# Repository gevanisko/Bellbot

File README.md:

# BellBot

This repository contains the hardware design files, documentation, and supporting resources for the BellBot project. BellBot is an autonomous luggage transportation robot intended to use sensing, mapping, wireless control, onboard data storage, and motor control to move luggage through indoor environments.

The hardware in this repository is developed across multiple board revisions. Each version is used to test, validate, and improve different parts of the system, including power regulation, peripheral integration, motor control, communication, and future onboard intelligence.

## Project Overview

The long-term goal of BellBot is to create a robotic luggage transportation system capable of navigating indoor environments. The system is designed around Simultaneous Localization and Mapping (SLAM), LiDAR sensing, inertial measurement, Bluetooth control, onboard logging, and multi-directional motor control.

Early board revisions focus on creating a reliable minimum viable product (MVP). Later revisions are intended to improve size, integration, efficiency, and performance.

## Core Goals

The BellBot hardware is designed to support:

- Autonomous navigation through mapped environments
- LiDAR-based obstacle detection and mapping
- Remote control through Bluetooth or another wireless interface
- Onboard storage for sensor data, logs, and system debugging
- Motor control for movement in a 2D plane
- Multiple regulated voltage rails for sensors, logic, and motors
- Expandability for future sensors, memory, and processing hardware

## Hardware Features

Across the project revisions, the BellBot hardware may include:

| Feature | Purpose |
|---|---|
| STM32 Microcontroller | Main control platform for peripherals, motor control, and system logic |
| LiDAR | 2D scanning for mapping, localization, and obstacle detection |
| IMU | Acceleration, angular velocity, magnetic field, and orientation sensing |
| Bluetooth / Wireless Module | Remote control, debugging, or wireless communication |
| SPI Flash / SD Storage | Onboard storage for sensor data and logs |
| Servo / Motor PWM Outputs | Control signals for the robot drive system |
| 3.3 V Rail | Logic-level supply for MCU and low-voltage peripherals |
| 5 V Rail | Peripheral and module power |
| 8 V Rail | Servo or motor power |
| I2C / SPI / UART / Quad-SPI Breakouts | Expansion for additional sensors, memory, or communication modules |
| Battery Charging and Protection | Portable operation and safe lithium-ion battery use |

Later iterations (V2 and onward) are looking to employ AI accelerated MCU chips (STM32 N6) with a reduced size and mainly using SMT components as opposed to through hole components

## Board Revisions

This repository is intended to support multiple hardware revisions. Each revision may include different component choices, layouts, and design improvements.

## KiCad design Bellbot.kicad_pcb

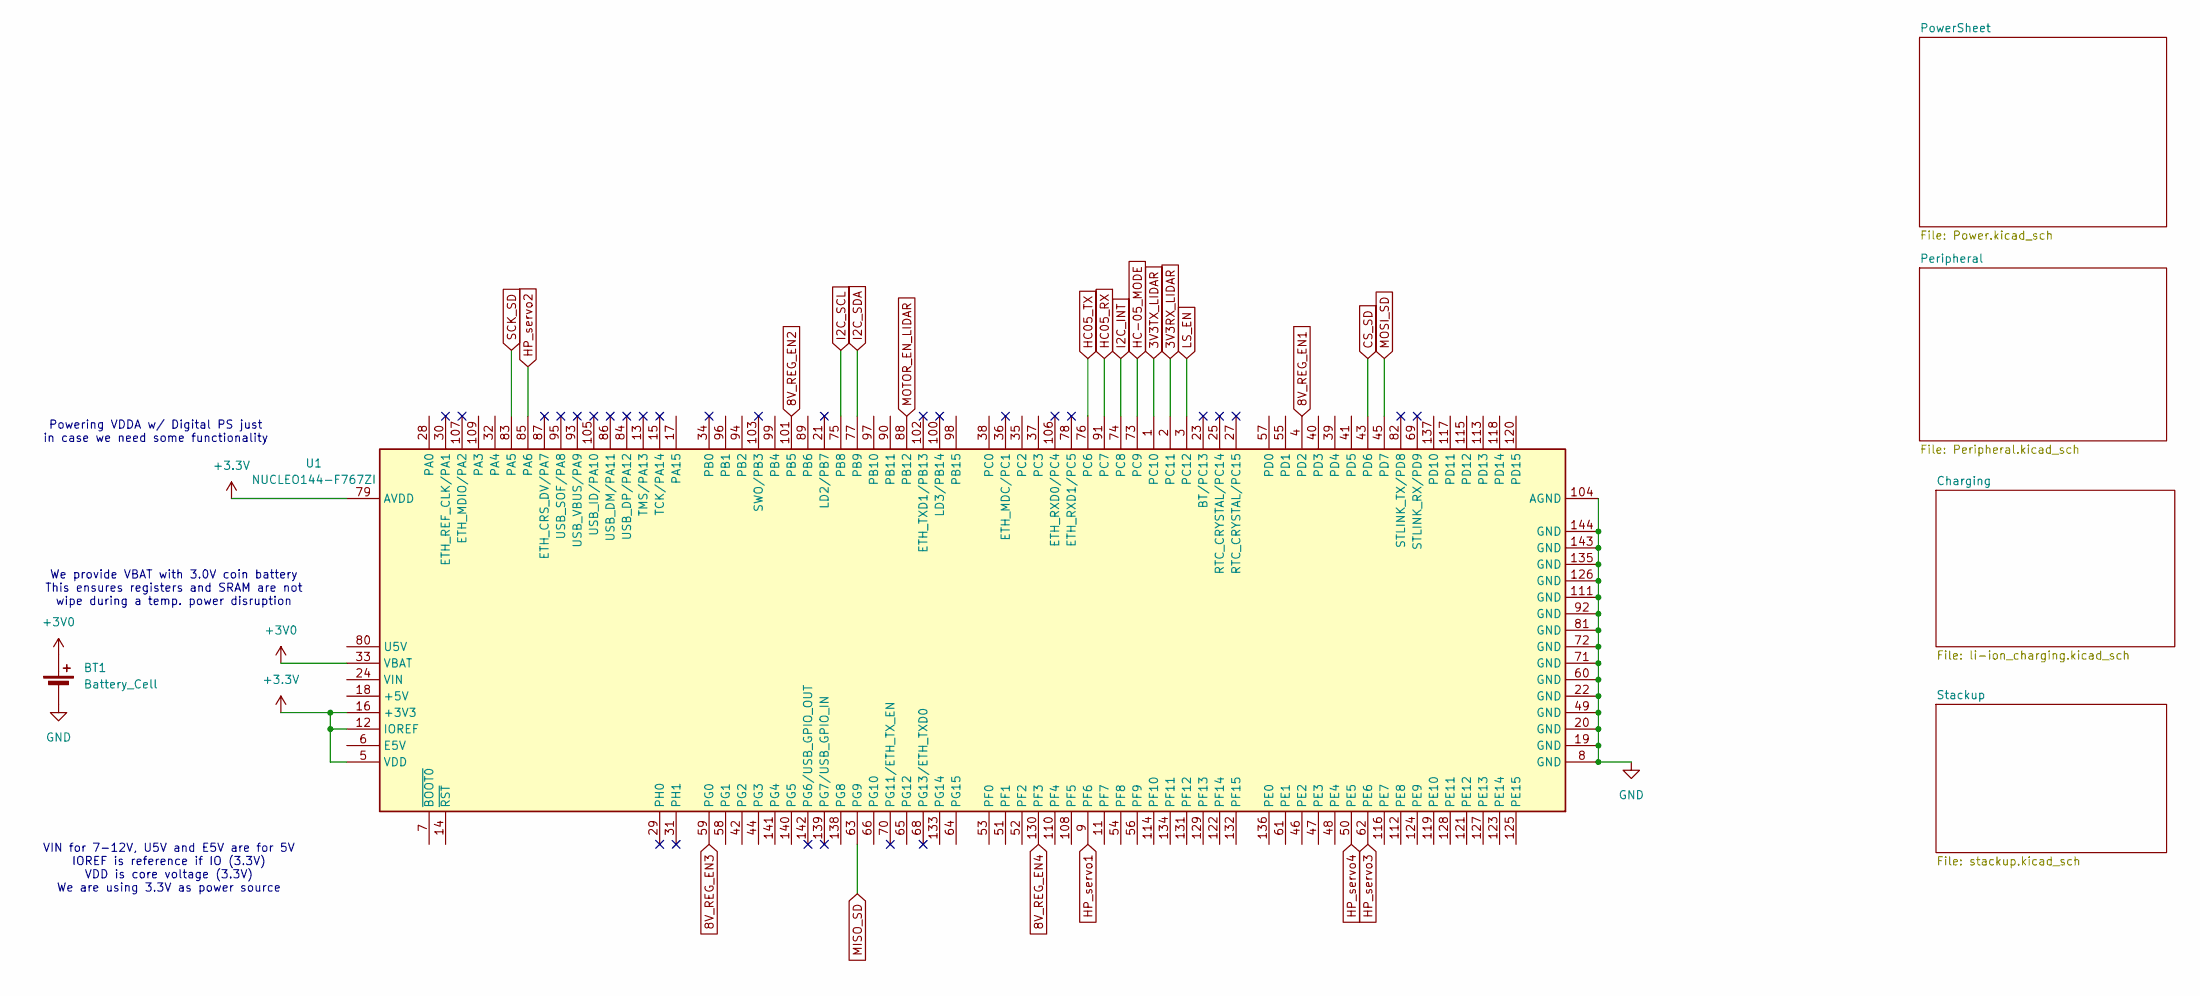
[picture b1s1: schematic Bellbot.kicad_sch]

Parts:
BT1: Battery_Cell; BatteryHolder_MPD_BC2003_1x2032
U1: NUCLEO144-F767ZI; ST_Morpho_Connector_144_STLink

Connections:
3V3RX_LIDAR: U1.2 (PC11); also elsewhere on the board
3V3TX_LIDAR: U1.1 (PC10); also elsewhere on the board
8V_REG_EN1: U1.4 (PD2); also elsewhere on the board
8V_REG_EN2: U1.101 (PB5); also elsewhere on the board
8V_REG_EN3: U1.59 (PG0); also elsewhere on the board
8V_REG_EN4: U1.130 (PF3); also elsewhere on the board
+3.3V: U1.5 (VDD), U1.12 (IOREF), U1.16 (+3V3), U1.79 (AVDD); also elsewhere on the board
+3V0: BT1.1 (+), U1.33 (VBAT)
/GPIO_Gen0: U1.116 (PE7)
/GPIO_Gen1: U1.112 (PE8)
/GPIO_Gen2: U1.124 (PE9)
/GPIO_Gen3: U1.119 (PE10)
/GPIO_Gen4: U1.128 (PE11)
/GPIO_Gen5: U1.121 (PE12)
/GPIO_Gen6: U1.127 (PE13)
/GPIO_Gen7: U1.123 (PE14)
/GPIO_Gen8: U1.125 (PE15)
CS_SD: U1.43 (PD6); also elsewhere on the board
GND: BT1.2 (-), U1.8 (GND), U1.19 (GND), U1.20 (GND), U1.22 (GND), U1.49 (GND), U1.60 (GND), U1.71 (GND), U1.72 (GND), U1.81 (GND), U1.92 (GND), U1.104 (AGND), U1.111 (GND), U1.126 (GND), U1.135 (GND), U1.143 (GND), U1.144 (GND); also elsewhere on the board
HC05_RX: U1.91 (PC7); also elsewhere on the board
HC05_TX: U1.76 (PC6); also elsewhere on the board
HC-05_MODE: U1.73 (PC9); also elsewhere on the board
HP_servo1: U1.9 (PF6); also elsewhere on the board
HP_servo2: U1.85 (PA6); also elsewhere on the board
HP_servo3: U1.62 (PE6); also elsewhere on the board
HP_servo4: U1.50 (PE5); also elsewhere on the board
I2C_Extra_SCL: U1.122 (PF14); also elsewhere on the board
I2C_Extra_SDA: U1.132 (PF15); also elsewhere on the board
I2C_INT: U1.74 (PC8); also elsewhere on the board
I2C_SCL: U1.75 (PB8); also elsewhere on the board
I2C_SDA: U1.77 (PB9); also elsewhere on the board
LS_EN: U1.3 (PC12)
MISO_SD: U1.63 (PG9); also elsewhere on the board
MOSI_SD: U1.45 (PD7); also elsewhere on the board
MOTOR_EN_LIDAR: U1.88 (PB12); also elsewhere on the board
unnamed 65: U1.44 (PG3); also elsewhere on the board
QUADSPI_CLK: U1.114 (PF10); also elsewhere on the board
QUADSPI_IO0: U1.54 (PF8); also elsewhere on the board
QUADSPI_IO1: U1.56 (PF9); also elsewhere on the board
QUADSPI_IO2: U1.46 (PE2); also elsewhere on the board
QUADSPI_IO3: U1.113 (PD13); also elsewhere on the board
QUADSPI_NCS: U1.97 (PB10); also elsewhere on the board
SCK_SD: U1.83 (PA5); also elsewhere on the board

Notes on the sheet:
VIN for 7-12V, U5V and E5V are for 5V IOREF is reference if IO (3.3V) VDD is core voltage (3.3V) We are using 3.3V as power source
Powering VDDA w/ Digital PS just in case we need some functionality
We provide VBAT with 3.0V coin battery This ensures registers and SRAM are not wipe during a temp. power disruption

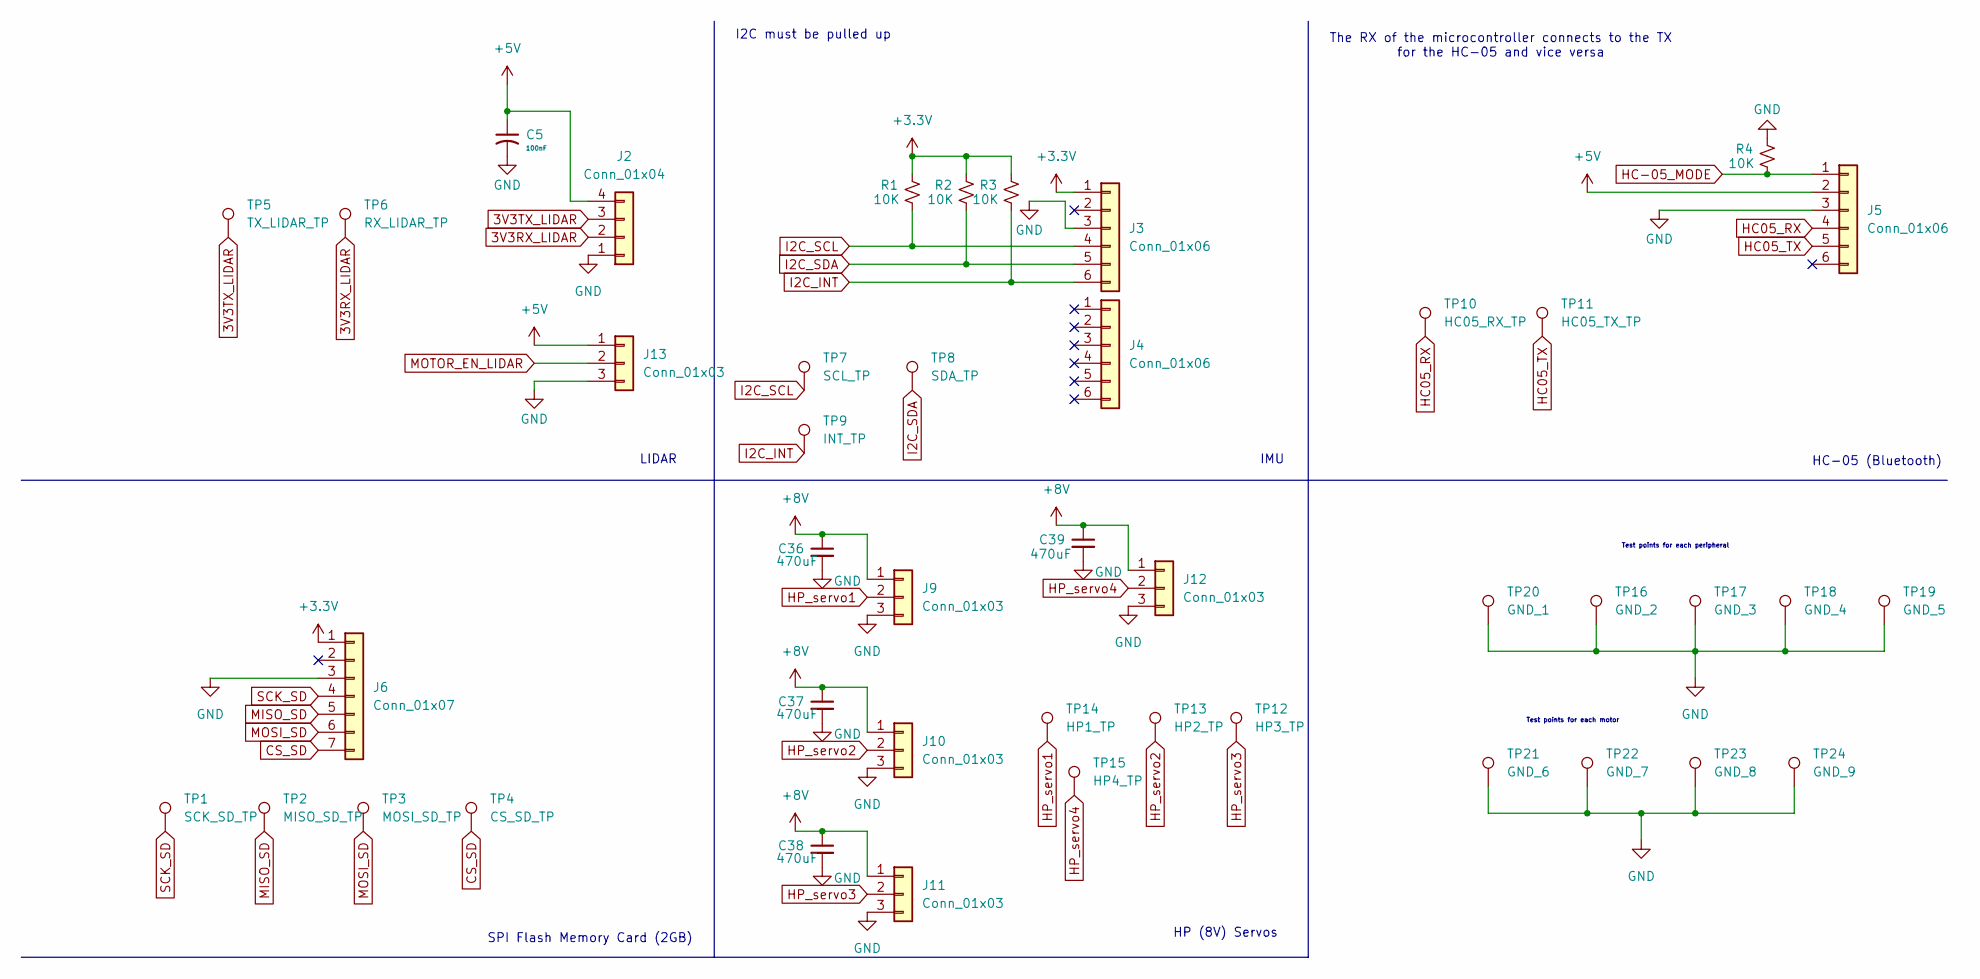
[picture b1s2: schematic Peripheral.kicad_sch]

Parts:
C5: 100nF; C_0603_1608Metric_Pad1.08x0.95mm_HandSolder
C36, C37, C38, C39: 470uF; C_0603_1608Metric_Pad1.08x0.95mm_HandSolder
J2: Conn_01x04; PinHeader_1x04_P2.54mm_Vertical
J3, J4, J5: Conn_01x06; PinHeader_1x06_P2.54mm_Vertical
J6: Conn_01x07; PinHeader_1x07_P2.54mm_Vertical
J9, J10, J11, J12, J13: Conn_01x03; PinHeader_1x03_P2.54mm_Vertical
R1, R2, R3, R4: 10K; R_0805_2012Metric_Pad1.20x1.40mm_HandSolder
TP1: SCK_SD_TP
TP2: MISO_SD_TP
TP3: MOSI_SD_TP
TP4: CS_SD_TP
TP5: TX_LIDAR_TP
TP6: RX_LIDAR_TP
TP7: SCL_TP
TP8: SDA_TP
TP9: INT_TP
TP10: HC05_RX_TP
TP11: HC05_TX_TP
TP12: HP3_TP
TP13: HP2_TP
TP14: HP1_TP
TP15: HP4_TP
TP16: GND_2
TP17: GND_3
TP18: GND_4
TP19: GND_5
TP20: GND_1
TP21: GND_6
TP22: GND_7
TP23: GND_8
TP24: GND_9

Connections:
3V3RX_LIDAR: J2.2, TP6.1 (1_1); also elsewhere on the board
3V3TX_LIDAR: J2.3, TP5.1 (1_1); also elsewhere on the board
+3.3V: J3.1, J6.1, R1.1, R2.1, R3.1; also elsewhere on the board
+5V: C5.1, J2.4, J5.2, J13.1; also elsewhere on the board
+8V: C36.1, C37.1, C38.1, C39.1, J9.1, J10.1, J11.1, J12.1; also elsewhere on the board
CS_SD: J6.7, TP4.1 (1_1); also elsewhere on the board
GND: C5.2, C36.2, C37.2, C38.2, C39.2, J2.1, J3.3, J5.3, J6.3, J9.3, J10.3, J11.3, J12.3, J13.3, R4.1, TP16.1 (1_1), TP17.1 (1_1), TP18.1 (1_1), TP19.1 (1_1), TP20.1 (1_1), TP21.1 (1_1), TP22.1 (1_1), TP23.1 (1_1), TP24.1 (1_1); also elsewhere on the board
HC05_RX: J5.4, TP10.1 (1_1); also elsewhere on the board
HC05_TX: J5.5, TP11.1 (1_1); also elsewhere on the board
HC-05_MODE: J5.1, R4.2; also elsewhere on the board
HP_servo1: J9.2, TP14.1 (1_1); also elsewhere on the board
HP_servo2: J10.2, TP13.1 (1_1); also elsewhere on the board
HP_servo3: J11.2, TP12.1 (1_1); also elsewhere on the board
HP_servo4: J12.2, TP15.1 (1_1); also elsewhere on the board
I2C_INT: J3.6, R3.2, TP9.1 (1_1); also elsewhere on the board
I2C_SCL: J3.4, R1.2, TP7.1 (1_1); also elsewhere on the board
I2C_SDA: J3.5, R2.2, TP8.1 (1_1); also elsewhere on the board
MISO_SD: J6.5, TP2.1 (1_1); also elsewhere on the board
MOSI_SD: J6.6, TP3.1 (1_1); also elsewhere on the board
MOTOR_EN_LIDAR: J13.2; also elsewhere on the board
SCK_SD: J6.4, TP1.1 (1_1); also elsewhere on the board

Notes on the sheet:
HC-05 (Bluetooth)
Test points for each motor
The RX of the microcontroller connects to the TX for the HC-05 and vice versa
Test points for each peripheral
IMU
LIDAR
HP (8V) Servos
I2C must be pulled up
SPI Flash Memory Card (2GB)

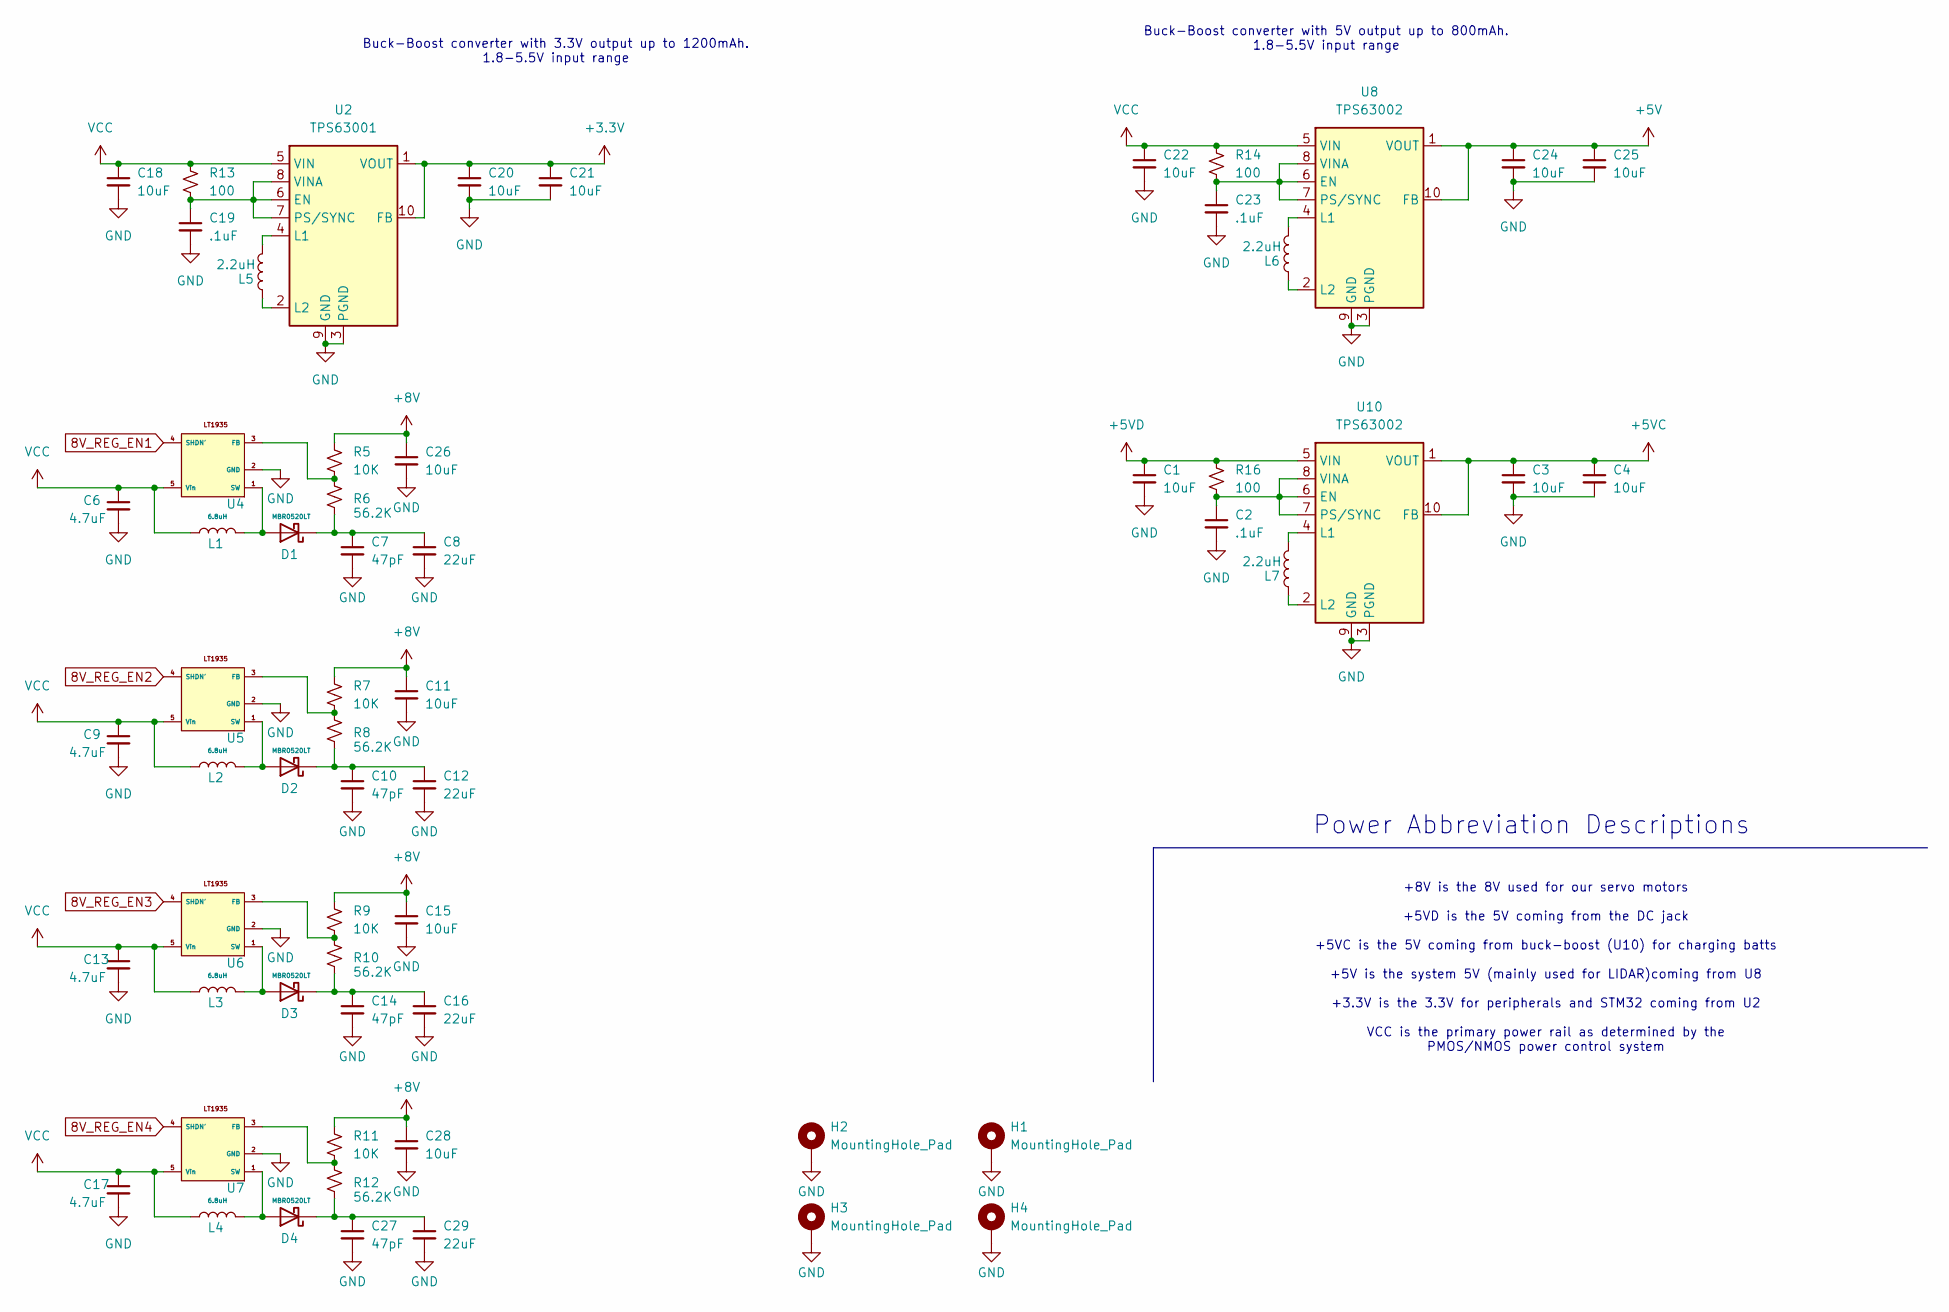
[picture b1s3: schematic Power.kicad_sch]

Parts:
C1, C3, C4, C11, C15, C18, C20, C21, C22, C24, C25, C26, C28: 10uF; C_0603_1608Metric_Pad1.08x0.95mm_HandSolder
C2, C19, C23: .1uF; C_0603_1608Metric_Pad1.08x0.95mm_HandSolder
C6, C9, C13, C17: 4.7uF; C_0603_1608Metric_Pad1.08x0.95mm_HandSolder
C7, C10, C14, C27: 47pF; C_0603_1608Metric_Pad1.08x0.95mm_HandSolder
C8, C12, C16, C29: 22uF; C_0603_1608Metric_Pad1.08x0.95mm_HandSolder
D1, D2, D3, D4: MBR0520LT; D_SOD-123
H1, H2, H3, H4: MountingHole_Pad; MountingHole_2.2mm_M2_DIN965_Pad
L1, L2, L3, L4: 6.8uH; NR6020T6R8
L5, L6, L7: 2.2uH; IND_VLS4012ET-2R2M-CA
R5, R7, R9, R11: 10K; R_0805_2012Metric_Pad1.20x1.40mm_HandSolder
R6, R8, R10, R12: 56.2K; R_0805_2012Metric_Pad1.20x1.40mm_HandSolder
R13, R14, R16: 100; R_0805_2012Metric_Pad1.20x1.40mm_HandSolder
U2: TPS63001; Texas_DRC0010J_ThermalVias
U4, U5, U6, U7: LT1935
U8, U10: TPS63002; Texas_DRC0010J_ThermalVias

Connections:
8V_REG_EN1: U4.4 (SHDN'); also elsewhere on the board
8V_REG_EN2: U5.4 (SHDN'); also elsewhere on the board
8V_REG_EN3: U6.4 (SHDN'); also elsewhere on the board
8V_REG_EN4: U7.4 (SHDN'); also elsewhere on the board
+3.3V: C20.1, C21.1, U2.1 (VOUT), U2.10 (FB); also elsewhere on the board
+5V: C24.1, C25.1, U8.1 (VOUT), U8.10 (FB); also elsewhere on the board
+5VC: C3.1, C4.1, U10.1 (VOUT), U10.10 (FB); also elsewhere on the board
+5VD: C1.1, C6.1, C9.1, C13.1, C17.1, C18.1, C22.1, L1.1, L2.1, L3.1, L4.1, R13.1, R14.1, R16.1, U2.5 (VIN), U4.5 (Vin), U5.5 (Vin), U6.5 (Vin), U7.5 (Vin), U8.5 (VIN), U10.5 (VIN); also elsewhere on the board
+8V: C11.1, C15.1, C26.1, C28.1, R5.1, R7.1, R9.1, R11.1; also elsewhere on the board
GND: C1.2, C2.2, C3.2, C4.2, C6.2, C7.2, C8.2, C9.2, C10.2, C11.2, C12.2, C13.2, C14.2, C15.2, C16.2, C17.2, C18.2, C19.2, C20.2, C21.2, C22.2, C23.2, C24.2, C25.2, C26.2, C27.2, C28.2, C29.2, H1.1 (1_1), H2.1 (1_1), H3.1 (1_1), H4.1 (1_1), U2.3 (PGND), U2.9 (GND), U2.11 (PGND), U4.2 (GND), U5.2 (GND), U6.2 (GND), U7.2 (GND), U8.3 (PGND), U8.9 (GND), U8.11 (PGND), U10.3 (PGND), U10.9 (GND), U10.11 (PGND); also elsewhere on the board
unnamed: D1.2 (A), L1.2, U4.1 (SW)
unnamed: C7.1, C8.1, D1.1 (K), R6.2
unnamed: D2.2 (A), L2.2, U5.1 (SW)
unnamed: C10.1, C12.1, D2.1 (K), R8.2
unnamed: D3.2 (A), L3.2, U6.1 (SW)
unnamed: C14.1, C16.1, D3.1 (K), R10.2
unnamed: D4.2 (A), L4.2, U7.1 (SW)
unnamed: C27.1, C29.1, D4.1 (K), R12.2
unnamed: C19.1, R13.2, U2.6 (EN), U2.7 (PS/SYNC), U2.8 (VINA)
unnamed: L5.2, U2.4 (L1)
unnamed: L5.1, U2.2 (L2)
unnamed: R5.2, R6.1, U4.3 (FB)
unnamed: R7.2, R8.1, U5.3 (FB)
unnamed: R9.2, R10.1, U6.3 (FB)
unnamed: R11.2, R12.1, U7.3 (FB)
unnamed: C23.1, R14.2, U8.6 (EN), U8.7 (PS/SYNC), U8.8 (VINA)
unnamed: L6.2, U8.4 (L1)
unnamed: L6.1, U8.2 (L2)
unnamed: C2.1, R16.2, U10.6 (EN), U10.7 (PS/SYNC), U10.8 (VINA)
unnamed: L7.2, U10.4 (L1)
unnamed: L7.1, U10.2 (L2)

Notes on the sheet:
Buck-Boost converter with 3.3V output up to 1200mAh. 1.8-5.5V input range
+8V is the 8V used for our servo motors +5VD is the 5V coming from the DC jack +5VC is the 5V coming from buck-boost (U10) for charging batts +5V is the system 5V (mainly used for LIDAR)coming from U8 +3.3V is the 3.3V for peripherals and STM32 coming from U2 VCC is the primary power rail as determ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
Power Abbreviation Descriptions
Buck-Boost converter with 5V output up to 800mAh. 1.8-5.5V input range

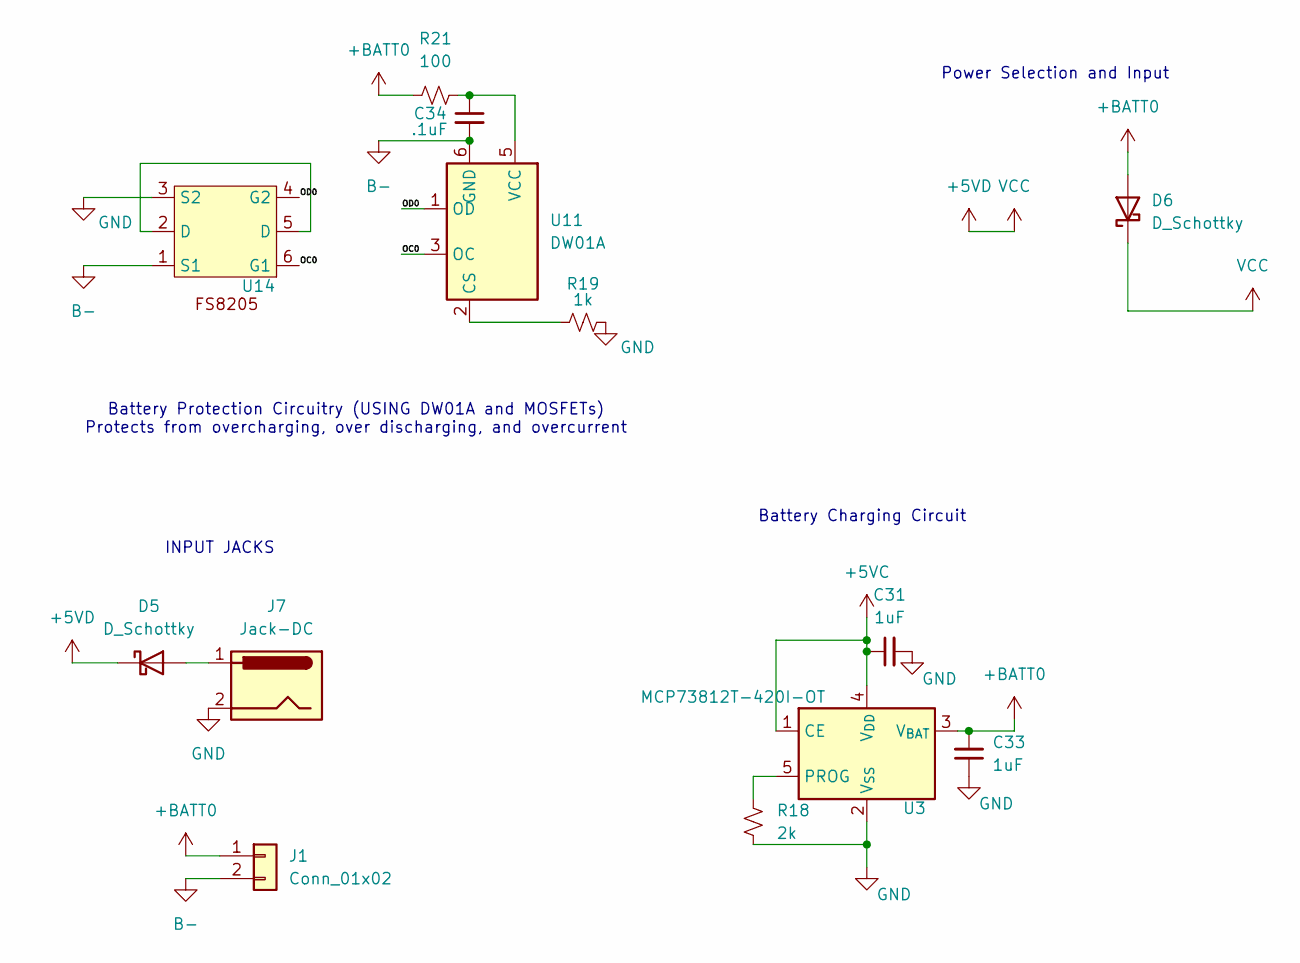
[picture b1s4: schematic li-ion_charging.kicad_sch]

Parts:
C31, C33: 1uF; C_0603_1608Metric_Pad1.08x0.95mm_HandSolder
C34: .1uF; C_0603_1608Metric_Pad1.08x0.95mm_HandSolder
D5, D6: D_Schottky; D_3220_8050Metric_Pad2.65x5.15mm_HandSolder
J1: Conn_01x02; PinHeader_1x02_P2.54mm_Vertical
J7: Jack-DC; BarrelJack_CUI_PJ-063AH_Horizontal
R18: 2k; R_0805_2012Metric_Pad1.20x1.40mm_HandSolder
R19: 1k; R_0805_2012Metric_Pad1.20x1.40mm_HandSolder
R21: 100; R_0805_2012Metric_Pad1.20x1.40mm_HandSolder
U3: MCP73812T-420I-OT; SOT-23-5
U11: DW01A; SOT-23-6
U14: SOT-23-6_Handsoldering

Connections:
+5VC: C31.1, U3.1 (CE), U3.4 (V_{DD}); also elsewhere on the board
+5VD: D5.1 (K), D6.1 (K); also elsewhere on the board
+BATT0: C33.2, D6.2 (A), J1.1, R21.1, U3.3 (V_{BAT})
/Charging/OC0: U11.3 (OC), U14.6 (G1)
/Charging/OD0: U11.1 (OD), U14.4 (G2)
B-: C34.2, J1.2, U11.6 (GND), U14.1 (S1)
GND: C31.2, C33.1, J7.2, R18.2, R19.2, U3.2 (V_{SS}), U14.3 (S2); also elsewhere on the board
unnamed: D5.2 (A), J7.1
unnamed: R18.1, U3.5 (PROG)
unnamed: R19.1, U11.2 (CS)
unnamed: C34.1, R21.2, U11.5 (VCC)
unnamed: U14.2 (D), U14.5 (D)

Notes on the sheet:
Battery Protection Circuitry (USING DW01A and MOSFETs) Protects from overcharging, over discharging, and overcurrent
Battery Charging Circuit
Power Selection and Input
INPUT JACKS

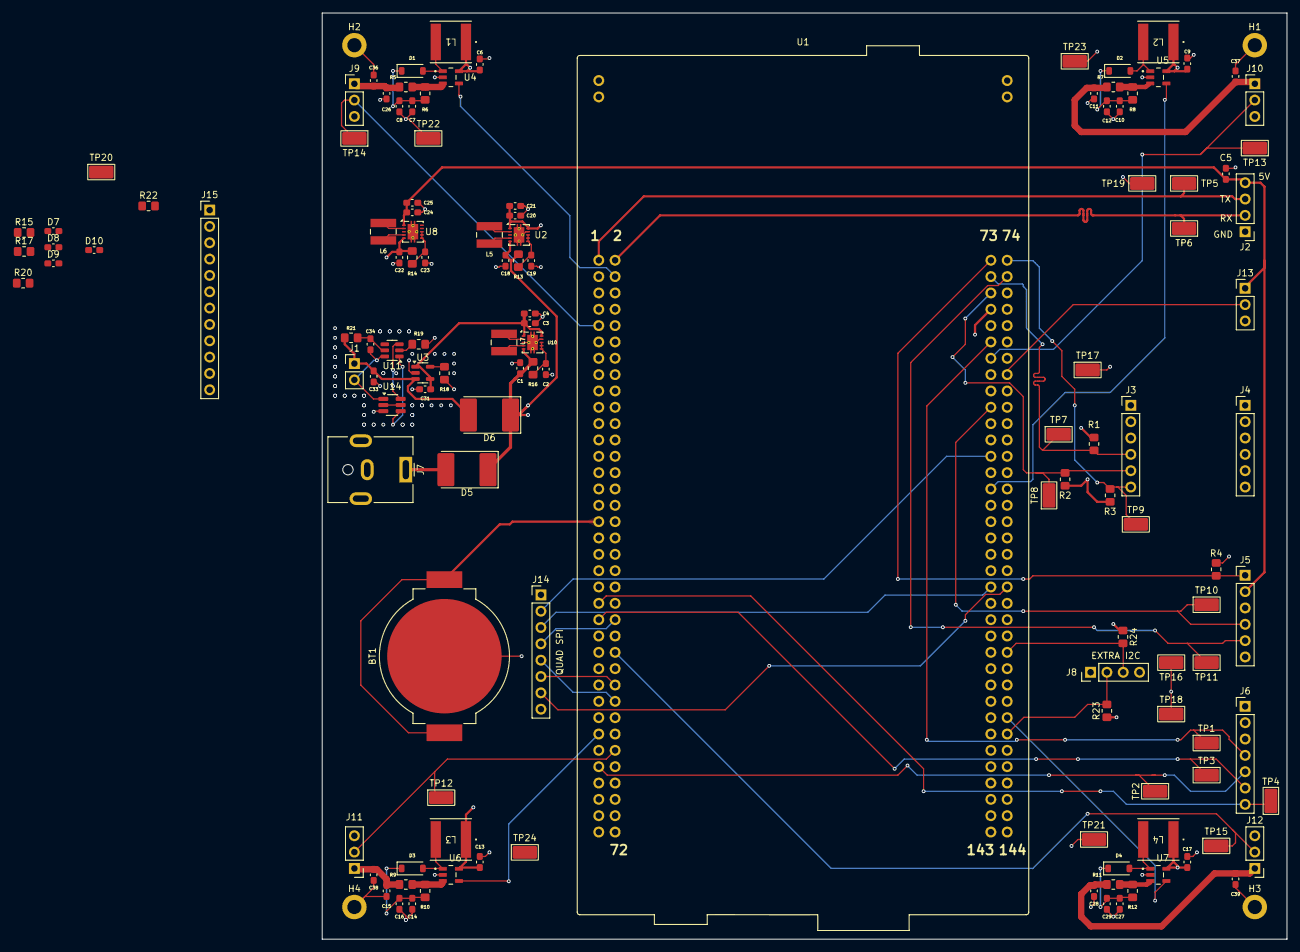
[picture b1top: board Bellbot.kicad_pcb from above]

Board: 4 copper layers, 150.0 x 144.0 mm, 132 parts (0 on the bottom side), 71 nets.

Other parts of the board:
D7, D8, D9, D10: LED; C_0603_1608Metric_Pad1.08x0.95mm_HandSolder
J8: Conn_01x04; PinHeader_1x04_P2.54mm_Vertical
J14: Conn_01x08; PinHeader_1x08_P2.54mm_Vertical
J15: Conn_01x12; PinHeader_1x12_P2.54mm_Vertical
R15, R22: 65; R_0805_2012Metric_Pad1.20x1.40mm_HandSolder
R17, R20: 150; R_0805_2012Metric_Pad1.20x1.40mm_HandSolder
R23, R24: 10K; R_0805_2012Metric_Pad1.20x1.40mm_HandSolder

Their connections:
+3.3V: J8.4, J14.1, J15.1, J15.8, R15.1, R23.1, R24.1; also elsewhere on the board
+5V: R17.1; also elsewhere on the board
+5VC: R20.1; also elsewhere on the board
GND: D7.1 (K), D8.1 (K), D9.1 (K), D10.1 (K), J8.1, J14.8, J15.12; also elsewhere on the board
I2C_Extra_SCL: J8.3, R24.2; also elsewhere on the board
I2C_Extra_SDA: J8.2, R23.2; also elsewhere on the board
unnamed: D7.2 (A), R15.2
unnamed: D8.2 (A), R17.2
unnamed: D9.2 (A), R20.2
unnamed: D10.2 (A), R22.2
unnamed 65: R22.1; also elsewhere on the board
QUADSPI_CLK: J14.7; also elsewhere on the board
QUADSPI_IO0: J14.6; also elsewhere on the board
QUADSPI_IO1: J14.5; also elsewhere on the board
QUADSPI_IO2: J14.4; also elsewhere on the board
QUADSPI_IO3: J14.3; also elsewhere on the board
QUADSPI_NCS: J14.2; also elsewhere on the board

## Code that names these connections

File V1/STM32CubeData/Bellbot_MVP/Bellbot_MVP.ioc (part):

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Mcu.Name=STM32F767ZITx
Mcu.Package=LQFP144
Mcu.UserName=STM32F767ZITx
PA1.GPIOParameters=GPIO_Label
PA1.GPIO_Label=RMII_REF_CLK [LAN8742A-CZ-TR_REFCLK0]
PA1.Mode=RMII
PA1.Signal=ETH_REF_CLK
PA10.GPIOParameters=GPIO_Label
PA10.GPIO_Label=USB_ID
PA10.Signal=USB_OTG_FS_ID
PA11.GPIOParameters=GPIO_Label
PA11.GPIO_Label=USB_DM
PA11.Mode=Device_Only
PA11.Signal=USB_OTG_FS_DM
PA12.GPIOParameters=GPIO_Label
PA12.GPIO_Label=USB_DP
PA12.Mode=Device_Only
PA12.Signal=USB_OTG_FS_DP
PA13.GPIOParameters=GPIO_Label
PA13.GPIO_Label=TMS
PA13.Mode=Serial_Wire
PA13.Signal=SYS_JTMS-SWDIO
PA14.GPIOParameters=GPIO_Label
PA14.GPIO_Label=TCK
PA14.Mode=Serial_Wire
PA14.Signal=SYS_JTCK-SWCLK
PA2.GPIOParameters=GPIO_Label
PA2.GPIO_Label=RMII_MDIO [LAN8742A-CZ-TR_MDIO]
PA2.Mode=RMII
PA2.Signal=ETH_MDIO
PA5.GPIOParameters=GPIO_Label
PA5.GPIO_Label=SPI1_SCK-SDCARD
PA5.Mode=Full_Duplex_Master
PA5.Signal=SPI1_SCK
PA6.GPIOParameters=GPIO_Label
PA6.GPIO_Label=PWM_GEN 4
PA6.Signal=S_TIM13_CH1
PA7.GPIOParameters=GPIO_Label
PA7.GPIO_Label=RMII_CRS_DV [LAN8742A-CZ-TR_CRS_DV]
PA7.Mode=RMII
PA7.Signal=ETH_CRS_DV
PA8.GPIOParameters=GPIO_Label
PA8.GPIO_Label=USB_SOF [TP1]
PA8.Mode=Activate_SOF_FS
PA8.Signal=USB_OTG_FS_SOF
PA9.GPIOParameters=GPIO_Label
PA9.GPIO_Label=USB_VBUS
PA9.Mode=Activate_VBUS
PA9.Signal=USB_OTG_FS_VBUS
PB0.GPIOParameters=GPIO_Label
PB0.GPIO_Label=LD1 [Green]
PB0.Signal=GPIO_Output
PB10.Mode=Single Bank 1
PB10.Signal=QUADSPI_BK1_NCS
PB12.GPIOParameters=GPIO_Label
PB12.GPIO_Label=MOTOR_EN_LIDAR
PB12.Signal=GPIO_Output
PB13.GPIOParameters=GPIO_Label
PB13.GPIO_Label=RMII_TXD1 [LAN8742A-CZ-TR_TXD1]
PB13.Mode=RMII
PB13.Signal=ETH_TXD1
PB14.GPIOParameters=GPIO_Label
PB14.GPIO_Label=LD3 [Red]
PB14.Signal=GPIO_Output
PB3.Signal=SYS_JTDO-SWO
PB5.GPIOParameters=GPIO_Label
PB5.GPIO_Label=HP_EN_2
PB5.Signal=GPIO_Output
PB7.GPIOParameters=GPIO_Label
PB7.GPIO_Label=LD2 [Blue]
PB7.Signal=GPIO_Output
PB8.GPIOParameters=GPIO_Label
PB8.GPIO_Label=I2C1_SCL_IMU
PB8.Mode=I2C
PB8.Signal=I2C1_SCL
PB9.GPIOParameters=GPIO_Label
PB9.GPIO_Label=I2C1_SDA_IMU
PB9.Mode=I2C
PB9.Signal=I2C1_SDA
PC1.GPIOParameters=GPIO_Label
PC1.GPIO_Label=RMII_MDC [LAN8742A-CZ-TR_MDC]
PC1.Mode=RMII
PC1.Signal=ETH_MDC
PC10.GPIOParameters=GPIO_Label
PC10.GPIO_Label=UART4_LiDAR_TX
PC10.Mode=Asynchronous
PC10.Signal=UART4_TX
PC11.GPIOParameters=GPIO_Label
PC11.GPIO_Label=UART4_LiDAR_RX
PC11.Mode=Asynchronous
PC11.Signal=UART4_RX
PC12.GPIOParameters=GPIO_Label
PC12.GPIO_Label=GPIO_LS_EN
PC12.Signal=GPIO_Output
PC13.GPIOParameters=GPIO_Label
PC13.GPIO_Label=USER_Btn [B1]
PC13.Signal=GPXTI13
PC14/OSC32_IN.Mode=LSE-External-Oscillator
PC14/OSC32_IN.Signal=RCC_OSC32_IN
PC15/OSC32_OUT.Mode=LSE-External-Oscillator
PC15/OSC32_OUT.Signal=RCC_OSC32_OUT
PC4.GPIOParameters=GPIO_Label
PC4.GPIO_Label=RMII_RXD0 [LAN8742A-CZ-TR_RXD0]
PC4.Mode=RMII
PC4.Signal=ETH_RXD0
PC5.GPIOParameters=GPIO_Label
PC5.GPIO_Label=RMII_RXD1 [LAN8742A-CZ-TR_RXD1]
PC5.Mode=RMII
PC5.Signal=ETH_RXD1
PC6.GPIOParameters=GPIO_Label
PC6.GPIO_Label=USART6_HC-05_TX
PC6.Mode=Asynchronous
PC6.Signal=USART6_TX
PC7.GPIOParameters=GPIO_Label
PC7.GPIO_Label=USART6_HC-05_RX
PC7.Mode=Asynchronous
PC7.Signal=USART6_RX
PC8.GPIOParameters=GPIO_Label
PC8.GPIO_Label=GPIO_I2C_INT
PC8.Signal=GPXTI8
PC9.GPIOParameters=GPIO_Label
PC9.GPIO_Label=HC-05_Mode
PC9.Signal=GPIO_Output
PD13.Mode=Single Bank 1
PD13.Signal=QUADSPI_BK1_IO3
PD15.GPIOParameters=GPIO_Label
PD15.GPIO_Label=HP_EN_1
PD15.Signal=GPIO_Output
PD2.GPIOParameters=GPIO_Label
PD2.GPIO_Label=HP_EN_1
PD2.Signal=GPIO_Output
PD6.GPIOParameters=GPIO_Label
PD6.GPIO_Label=SPI1_CS_SDCARD
PD6.Signal=GPIO_Output
PD7.GPIOParameters=GPIO_Label
PD7.GPIO_Label=SPI1_MOSI_SDCARD
PD7.Mode=Full_Duplex_Master
PD7.Signal=SPI1_MOSI
PD8.GPIOParameters=GPIO_Label
PD8.GPIO_Label=STLK_RX [STM32F103CBT6_PA3]
PD8.Mode=Asynchronous
PD8.Signal=USART3_TX
PD9.GPIOParameters=GPIO_Label
PD9.GPIO_Label=STLK_TX [STM32F103CBT6_PA2]
PD9.Mode=Asynchronous
PD9.Signal=USART3_RX
PE10.GPIOParameters=GPIO_Label
PE10.GPIO_Label=Gen_GPIO1
PE10.Signal=GPIO_Output
PE11.GPIOParameters=GPIO_Label
PE11.GPIO_Label=Gen_GPIO2
PE11.Signal=GPIO_Output
PE12.GPIOParameters=GPIO_Label
PE12.GPIO_Label=Gen_GPIO3
PE12.Signal=GPIO_Output
PE13.GPIOParameters=GPIO_Label
PE13.GPIO_Label=Gen_GPIO4
PE13.Signal=GPIO_Output
PE14.GPIOParameters=GPIO_Label
PE14.GPIO_Label=Gen_GPIO5
PE14.Signal=GPIO_Output
PE15.GPIOParameters=GPIO_Label
PE15.GPIO_Label=Gen_GPIO6
PE15.Signal=GPIO_Output
PE2.Mode=Single Bank 1
PE2.Signal=QUADSPI_BK1_IO2
PE5.GPIOParameters=GPIO_Label
PE5.GPIO_Label=PWM_GEN 1
PE5.Signal=S_TIM9_CH1
PE6.GPIOParameters=GPIO_Label
PE6.GPIO_Label=PWM_GEN 2
PE6.Signal=S_TIM9_CH2
PE7.GPIOParameters=GPIO_Label
PE7.GPIO_Label=Gen_GPIO7
PE7.Signal=GPIO_Output
PE8.GPIOParameters=GPIO_Label
PE8.GPIO_Label=Gen_GPIO8
PE8.Signal=GPIO_Output
PE9.GPIOParameters=GPIO_Label
PE9.GPIO_Label=Gen_GPIO9
PE9.Signal=GPIO_Output
PF10.Mode=Single Bank 1
PF10.Signal=QUADSPI_CLK
PF14.Mode=I2C
PF14.Signal=I2C4_SCL
PF15.Mode=I2C
PF15.Signal=I2C4_SDA
PF3.GPIOParameters=GPIO_Label
PF3.GPIO_Label=HP_EN_4
PF3.Signal=GPIO_Output
PF6.GPIOParameters=GPIO_Label
PF6.GPIO_Label=PWM_GEN 3
PF6.Signal=S_TIM10_CH1
PF8.Mode=Single Bank 1
PF8.Signal=QUADSPI_BK1_IO0
PF9.Mode=Single Bank 1
PF9.Signal=QUADSPI_BK1_IO1
PG0.GPIOParameters=GPIO_Label
PG0.GPIO_Label=HP_EN_3
PG0.Signal=GPIO_Output
PG11.GPIOParameters=GPIO_Label
PG11.GPIO_Label=RMII_TX_EN [LAN8742A-CZ-TR_TXEN]
PG11.Mode=RMII
PG11.Signal=ETH_TX_EN
PG13.GPIOParameters=GPIO_Label
PG13.GPIO_Label=RMII_TXD0 [LAN8742A-CZ-TR_TXD0]
PG13.Mode=RMII
PG13.Signal=ETH_TXD0
PG3.GPIOParameters=GPIO_Label
PG3.GPIO_Label=TEST LED
PG3.Signal=GPIO_Output
PG6.GPIOParameters=GPIO_Label
PG6.GPIO_Label=USB_PowerSwitchOn [STMPS2151STR_EN]
PG6.Signal=GPIO_Output
PG7.GPIOParameters=GPIO_Label
PG7.GPIO_Label=USB_OverCurrent [STMPS2151STR_FAULT]
PG7.Signal=GPIO_Input
PG9.GPIOParameters=GPIO_Label
PG9.GPIO_Label=SPI1_MISO_SDCARD
PG9.Mode=Full_Duplex_Master
PG9.Signal=SPI1_MISO
PH0/OSC_IN.GPIOParameters=GPIO_Label
PH0/OSC_IN.GPIO_Label=MCO [STM32F103CBT6_PA8]
PH0/OSC_IN.Mode=HSE-External-Clock-Source
PH0/OSC_IN.Signal=RCC_OSC_IN
PH1/OSC_OUT.Mode=HSE-External-Clock-Source
PH1/OSC_OUT.Signal=RCC_OSC_OUT
RCC.HSE_VALUE=8000000
RCC.SYSCLKFreq_VALUE=96000000
RCC.SYSCLKSource=RCC_SYSCLKSOURCE_PLLCLK
RCC.SYSCLKSourceVirtual=RCC_SYSCLKSOURCE_PLLCLK
board=NUCLEO-F767ZI
boardIOC=true

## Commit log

2026-05-14 stm32cubeide files added
2026-05-14 General Layout Complete
    Completed general layout, beginning to add debugging components such as test points and
2026-05-15 update
    more work on testpoints
2026-05-15 testpoints on board
    Organized testpoints on board. Still need to fix bus for general purpose GPIO and route traces for LEDs.
2026-05-15 STM32 MX IoC update
    Still need to rename Gen GPIO pins to new bus names
2026-05-16 routed quad spi
2026-05-16 almost completed board
    need to clean up silkscreen, run thru checklist and verify, review datasheets
2026-05-16 cleanup
2026-05-17 completed v1 board with outputs
2026-05-17 cleanup and reorganizing
2026-05-18 Updated/Verified Values
2026-05-18 Documentation PDF Added
